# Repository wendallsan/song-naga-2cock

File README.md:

# Two-Headed Cockatrice  
### Double Deluxe Voltage Controlled Envelope Generator for Eurorack
  
Panel Concept Design  

## Features  
- Dual ADSR Envelopes with Gate and Trigger inputs and Voltage Control over each stage.  CV inputs for these controls are shared between both Envelopes with attenuverters for each for independently adjusting the resonse to incoming CV signals.  
- Envelope 2 includes a Voltage Controlled Gate Delay, and is triggered with Envelope 1 when nothing is plugged into its Gate or Trigger inputs.  
- Individual signal outputs for each Envelope and a Mix section, which outputs a mixed signal of both envelopes.  
- LED indicators of the output signals.  
- Fire button to manully trigger the Envelopes

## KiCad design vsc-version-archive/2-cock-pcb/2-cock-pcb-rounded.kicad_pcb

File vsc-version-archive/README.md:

# Two-Headed Cockatrice  
### Double Deluxe Voltage Controlled Envelope Generator for Eurorack

Panel Concept Design  

## Features  
- Dual ADSR Envelopes with Gate and Trigger inputs and Voltage Control over each stage.  CV inputs for these controls are shared between both Envelopes with attenuverters for each for independently adjusting the resonse to incoming CV signals.  
- Envelope 2 includes a Voltage Controlled Gate Delay, and is triggered with Envelope 1 when nothing is plugged into its Gate or Trigger inputs.  
- Individual signal outputs for each Envelope and a Mix section, which outputs a mixed signal of both envelopes.  
- LED indicators of the output signals.  
- Fire button to manully trigger the Envelopes

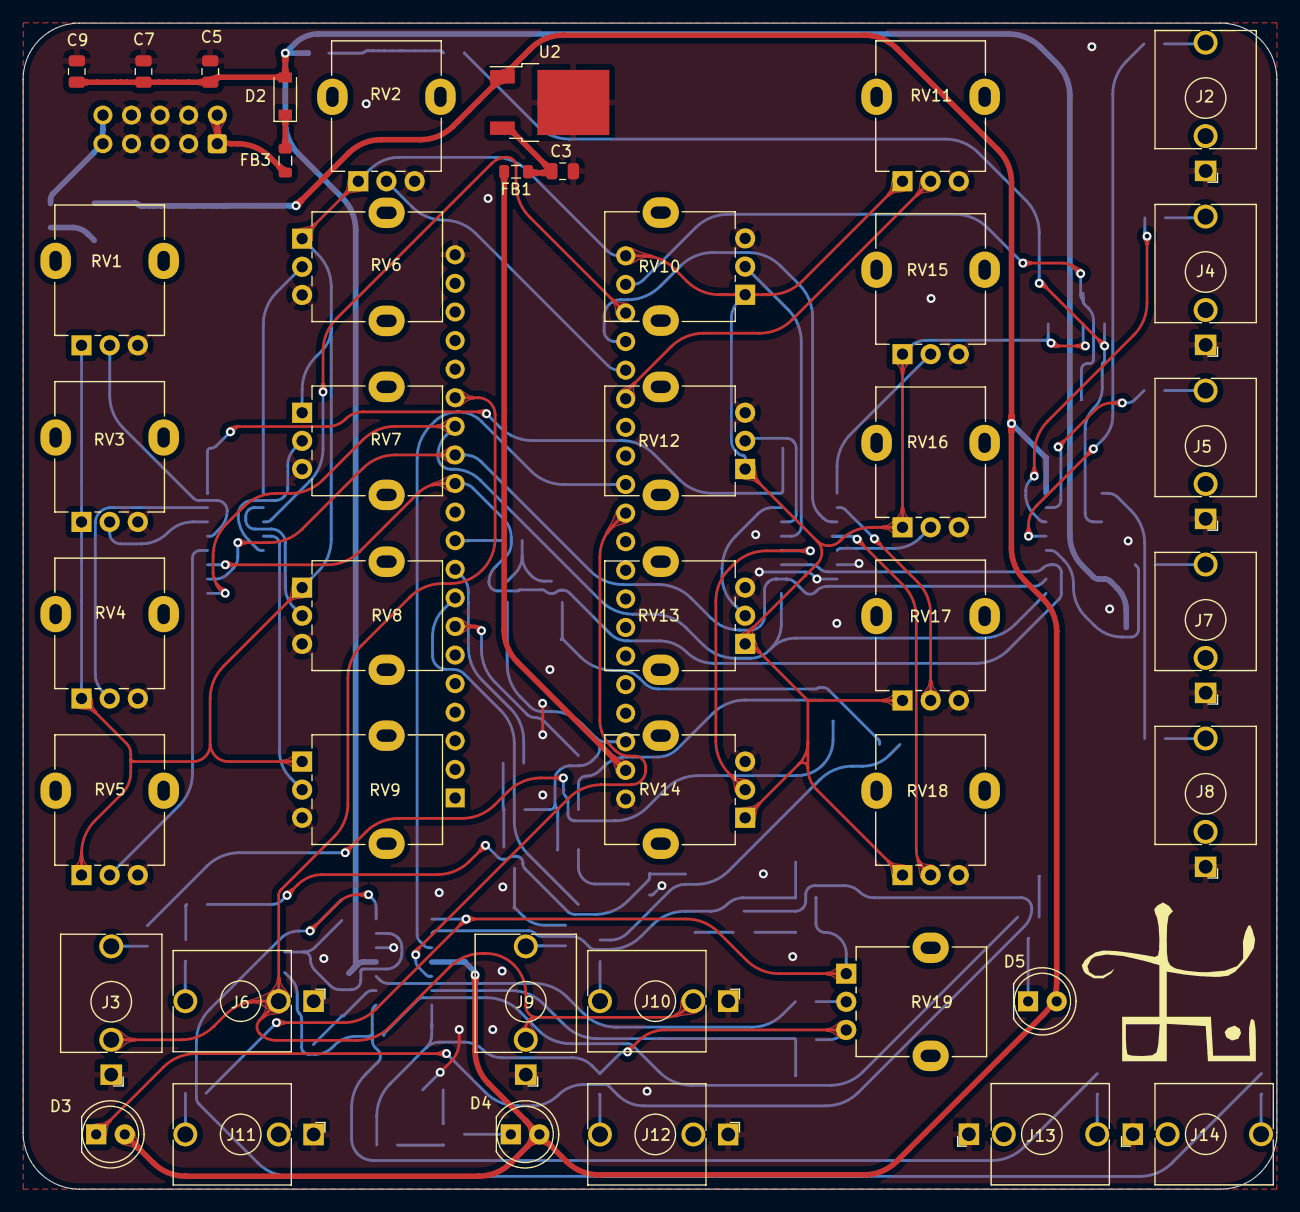
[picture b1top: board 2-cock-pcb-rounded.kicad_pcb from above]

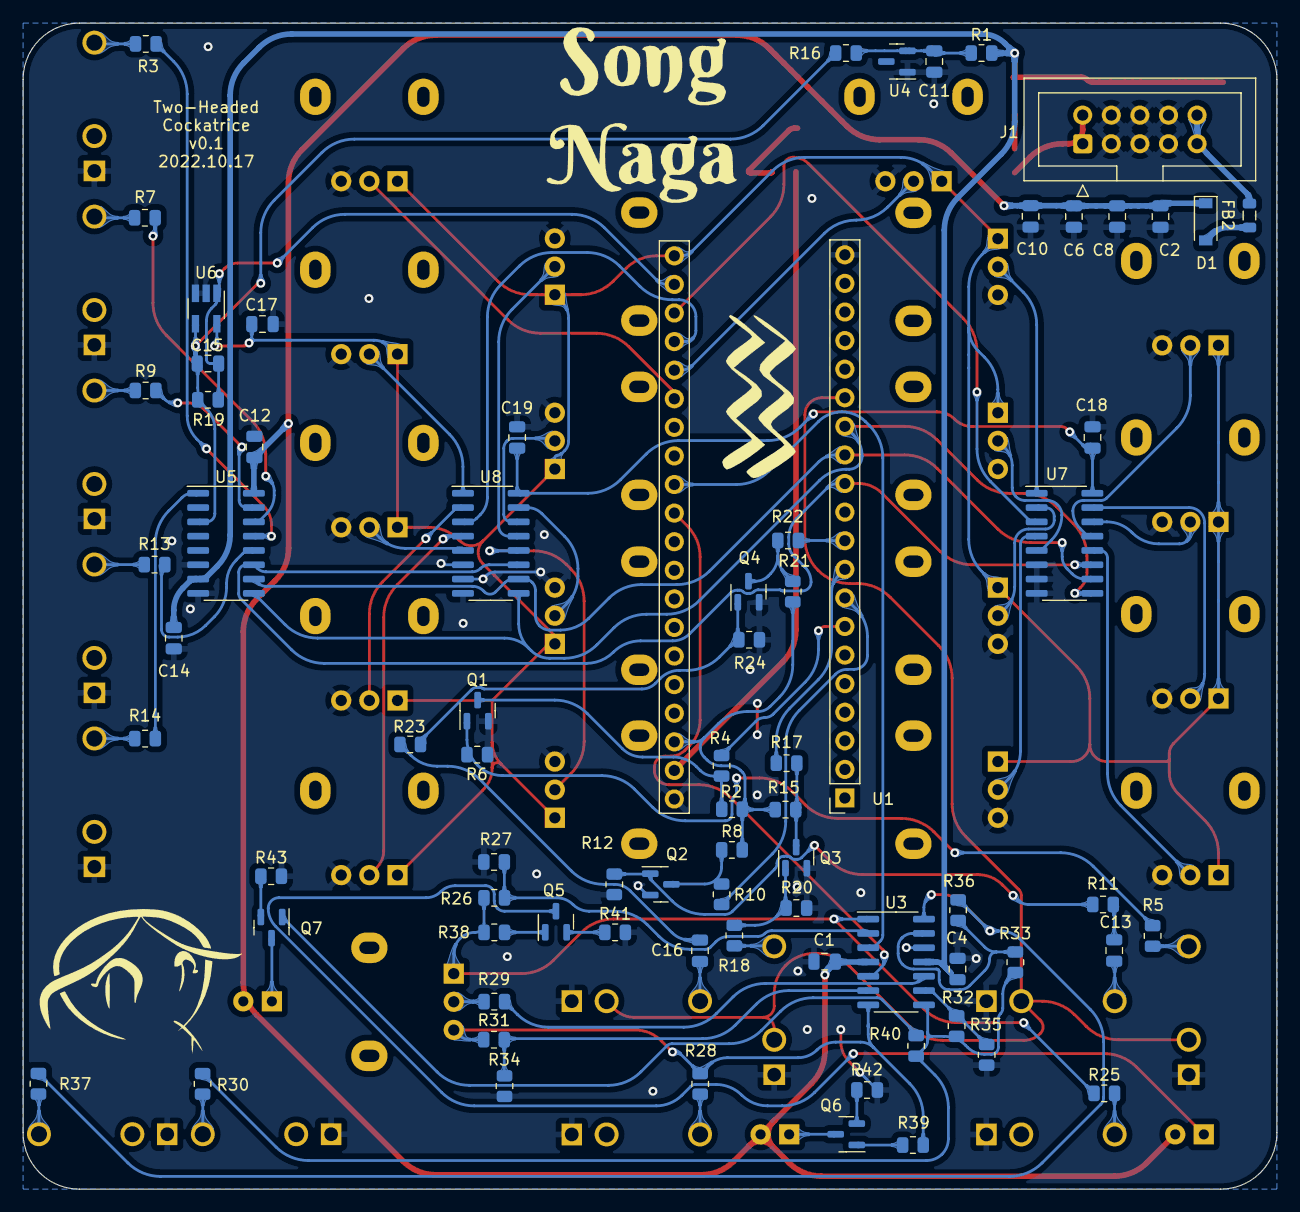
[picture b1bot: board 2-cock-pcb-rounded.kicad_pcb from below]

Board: 2 copper layers, 111.4 x 103.6 mm, 122 parts (78 on the bottom side), 92 nets.

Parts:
C1, C4, C12, C14, C15, C17, C18, C19: 10nF; C_0805_2012Metric
C2: 330nF; C_0805_2012Metric
C3, C7, C8, C9, C10, C11, C13, C16: 100nF; C_0805_2012Metric
C5, C6: 10uF; C_0805_2012Metric
D1, D2: D_Schottky; D_SOD-123
D3, D4, D5: LED; LED_D5.0mm
FB1, FB2, FB3: FerriteBead; L_0805_2012Metric
G1, G2, G3, G5: LOGO
J1: EURO_PWR_2x5; IDC-Header_2x05_P2.54mm_Vertical
J2: Delay CV In; Jack_3.5mm_QingPu_WQP-PJ398SM_Vertical_CircularHoles
J3: Gate 1; Jack_3.5mm_QingPu_WQP-PJ398SM_Vertical_CircularHoles
J4: Attack CV In; Jack_3.5mm_QingPu_WQP-PJ398SM_Vertical_CircularHoles
J5: Decay CV In; Jack_3.5mm_QingPu_WQP-PJ398SM_Vertical_CircularHoles
J6: Trigger 1; Jack_3.5mm_QingPu_WQP-PJ398SM_Vertical_CircularHoles
J7: Sustain CV In; Jack_3.5mm_QingPu_WQP-PJ398SM_Vertical_CircularHoles
J8: Release CV In; Jack_3.5mm_QingPu_WQP-PJ398SM_Vertical_CircularHoles
J9: Gate 2; Jack_3.5mm_QingPu_WQP-PJ398SM_Vertical_CircularHoles
J10: Trigger 2; Jack_3.5mm_QingPu_WQP-PJ398SM_Vertical_CircularHoles
J11: Out 1; Jack_3.5mm_QingPu_WQP-PJ398SM_Vertical_CircularHoles
J12: Out 2; Jack_3.5mm_QingPu_WQP-PJ398SM_Vertical_CircularHoles
J13: Mix Out; Jack_3.5mm_QingPu_WQP-PJ398SM_Vertical_CircularHoles
J14: Inv Out; Jack_3.5mm_QingPu_WQP-PJ398SM_Vertical_CircularHoles
Q1, Q2, Q3, Q4, Q5, Q6, Q7: MMBT3904; SOT-23
R1, R4, R10, R17, R22, R25, R28, R30, R37, R41, R42, R43: 1k; R_0805_2012Metric
R2, R15, R21, R38, R39, R40: 10k; R_0805_2012Metric
R3, R5, R7, R9, R11, R13, R14, R18, R23, R26, R29, R31, R32, R33, R35, R36: 100k; R_0805_2012Metric
R6, R12, R20, R24: 1M; R_0805_2012Metric
R8: R; R_0805_2012Metric
R16: 200k; R_0805_2012Metric
R19: 27k; R_0805_2012Metric
R27, R34: 50k; R_0805_2012Metric
RV1, RV2, RV3, RV4, RV5, RV6, RV7, RV8, RV9, RV10, RV11, RV12, RV13, RV14, RV15, RV16, RV17, RV18: 100k; Potentiometer_Alpha_RD901F-40-00D_Single_Vertical
RV19: B100k; Potentiometer_Alpha_RD901F-40-00D_Single_Vertical
U1: Daisy_Seed
U2: LM7805_TO220; TO-252-2
U3: TL074; SOIC-14_3.9x8.7mm_P1.27mm
U4: LM4040DBZ-10; SOT-23
U5, U7, U8: CD4051B; SOIC-16_3.9x9.9mm_P1.27mm
U6: MCP6001-OT; SOT-23-5_HandSoldering

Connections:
3V3_A: C17.1, RV1.1, RV2.1, RV3.1, RV4.1, RV5.1, RV6.1, RV7.1, RV8.1, RV9.1, RV10.1, RV11.1, RV12.1, RV13.1, RV14.1, RV15.1, RV16.1, RV17.1, RV18.1, U1.21 (+3V3_A), U6.5 (V+)
3V3_D: R2.2, R8.2, R15.2, R21.2, U1.38 (+3V3_D)
+3V3_A: C18.1, C19.1, U7.16 (VDD), U8.16 (VDD)
+5V: FB1.2, U1.39 (V_IN)
+12V: C1.1, C2.2, C6.1, C8.2, C10.2, C12.1, D1.1 (K), D3.2 (A), D4.2 (A), D5.2 (A), U2.1 (VI), U3.4 (V+), U5.16 (VDD)
-10V_REF: C11.2, R1.1, R16.1, U4.2 (A)
-12V: C4.1, C5.2, C7.1, C9.1, C14.1, D2.2 (A), R1.2, U3.11 (V-), U5.7 (VEE)
ADSR1_OUT: U1.29 (GPIO23(DAC1_OUT1)), U3.3 (+)
ADSR2_OUT: U1.30 (GPIO24(DAC1_OUT2)), U3.5 (+)
Attack 1: RV1.2, U7.13 (X0)
Attack 1 CV Adjust: RV10.2, U8.13 (X0)
Attack 2: RV6.2, U7.1 (X4)
Attack 2 CV Adjust: RV15.2, U8.1 (X4)
Attack CV: R7.2, U5.14 (X1)
CHANNEL SELECT A: U1.12 (GPIO12(I2C1_SCL)), U5.11 (A), U7.11 (A), U8.11 (A)
CHANNEL SELECT B: U1.13 (GPIO13(I2C1_SDA)), U5.10 (B), U7.10 (B), U8.10 (B)
CHANNEL SELECT C: U1.14 (GPIO14(USART1_TX)), U5.9 (C), U7.9 (C), U8.9 (C)
Decay 1: RV3.2, U7.14 (X1)
Decay 1 CV Adjust: RV12.2, U8.14 (X1)
Decay 2: RV7.2, U7.5 (X5)
Decay 2 CV Adjust: RV16.2, U8.5 (X5)
Decay CV: R9.2, U5.15 (X2)
Delay 2: RV2.2, U1.25 (GPIO19(ADC1_INP7))
Delay 2 CV Adjust: RV11.2, U1.26 (GPIO20(ADC1_INP3))
Delay CV: R3.2, U5.13 (X0)
GATE 1: R4.1, U1.7 (GPIO7(SDMMC1_CK))
GATE 2: R17.1, U1.9 (GPIO9(SPI1_SCK))
GND: C1.2, C2.1, C3.1, C4.2, C5.1, C6.2, C7.2, C8.1, C9.2, C10.1, C11.1, C12.2, C14.2, C17.2, C18.2, C19.2, J1.3 (GND), J1.4 (GND), J1.5 (GND), J1.6 (GND), J1.7 (GND), J1.8 (GND), J2.S, J3.S, J4.S, J5.S, J6.S, J7.S, J8.S, J9.S, J10.S, J11.S, J12.S, J13.S, J14.S, Q1.2 (E), Q2.2 (E), Q3.2 (E), Q4.2 (E), R6.1, R12.1, R20.1, R24.1, R27.1, R34.1, R35.1, R41.2, R42.2, R43.2, RV1.3, RV2.3, RV3.3, RV4.3, RV5.3, RV6.3, RV7.3, RV8.3, RV9.3, RV10.3, RV11.3, RV12.3, RV13.3, RV14.3, RV15.3, RV16.3, RV17.3, RV18.3, U1.20 (AGND), U1.40 (GND), U2.2 (GND), U3.12 (+), U4.1 (K), U5.6 (INH), U5.8 (VSS), U6.2 (V-), U6.3 (+), U7.6 (INH), U7.7 (VEE), U7.8 (VSS), U8.6 (INH), U8.7 (VEE), U8.8 (VSS)
MIX_LED: R30.1, R32.2, R33.1, R40.2, U3.8
MUXED SIGNAL 1: C15.2, R19.2, U1.22 (GPIO16(ADC1_INP10)), U6.1
MUXED SIGNAL 2: U1.23 (GPIO17(ADC1_INP15)), U7.3 (X)
MUXED SIGNAL 3: U1.24 (GPIO18(ADC1_INP5)), U8.3 (X)
NORMAL_PROBE: J3.TN, J6.TN, J9.TN, J10.TN, U1.15 (GPIO15(USART1_RX))
unnamed: C3.2, FB1.1, U2.3 (VO)
unnamed: C13.1, J6.T
unnamed: C13.2, R11.1
unnamed: C16.1, J10.T
unnamed: C16.2, R23.1
unnamed: D1.2 (A), FB2.2
unnamed: D2.1 (K), FB3.2
unnamed: D3.1 (K), Q5.3 (C)
unnamed: D4.1 (K), Q6.3 (C)
unnamed: D5.1 (K), Q7.3 (C)
unnamed: FB2.1, J1.9 (+12V), J1.10 (+12V)
unnamed: FB3.1, J1.1 (-12V), J1.2 (-12V)
unnamed: J2.T, R3.1
unnamed: J3.T, R5.1
unnamed: J4.T, R7.1
unnamed: J5.T, R9.1
unnamed: J7.T, R13.1
unnamed: J8.T, R14.1
unnamed: J9.T, R18.1
unnamed: J11.T, R25.2
unnamed: J12.T, R28.2
unnamed: J13.T, R30.2
unnamed: J14.T, R37.2
unnamed: Q1.1 (B), R5.2, R6.2
unnamed: Q1.3 (C), R2.1, R4.2
unnamed: Q2.1 (B), R11.2, R12.2
unnamed: Q2.3 (C), R8.1, R10.2
unnamed: Q3.1 (B), R18.2, R20.2
unnamed: Q3.3 (C), R15.1, R17.2
unnamed: Q4.1 (B), R23.2, R24.2
unnamed: Q4.3 (C), R21.1, R22.2
unnamed: Q5.1 (B), R38.1
unnamed: Q5.2 (E), R41.1
unnamed: Q6.1 (B), R39.1
unnamed: Q6.2 (E), R42.1
unnamed: Q7.1 (B), R40.1
unnamed: Q7.2 (E), R43.1
unnamed: R26.1, R27.2, U3.2 (-)
unnamed: R29.1, RV19.2
unnamed: R29.2, U3.10 (+)
unnamed: R31.1, R34.2, U3.6 (-)
unnamed: R32.1, R35.2, U3.9 (-)
unnamed: R33.2, R36.1, U3.13 (-)
unnamed: R36.2, R37.1, U3.14
OUT1_LED: R25.1, R26.2, R38.2, RV19.1, U3.1
OUT2_LED: R28.1, R31.2, R39.2, RV19.3, U3.7
Release 1: RV5.2, U7.12 (X3)
Release 1 CV Adjust: RV14.2, U8.12 (X3)
Release 2: RV9.2, U7.4 (X7)
Release 2 CV Adjust: RV18.2, U8.4 (X7)
Release CV: R14.2, U5.1 (X4)
Sustain 1: RV4.2, U7.15 (X2)
Sustain 1 CV Adjust: RV13.2, U8.15 (X2)
Sustain 2: RV8.2, U7.2 (X6)
Sustain 2 CV Adjust: RV17.2, U8.2 (X6)
Sustain CV: R13.2, U5.12 (X3)
TRIGGER 1: R10.1, U1.8 (GPIO8(SPI_NSS))
TRIGGER 2: R22.1, U1.10 (GPIO10(SPI1_MISO))
±10V MUXED SIGNAL: C15.1, R16.2, R19.1, U5.3 (X), U6.4 (-)

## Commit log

2022-08-17 initial commit. Basic working ADSR example with a button trigger.
2022-08-28 2cock.cpp: added mux handling, currently set up to handle adsr1 and adsr2 pots. Added adsr2. Added delaySignal ADC Channel for single input (doesn't fit on the mux). Updated DAC to output 2 channels 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
2022-09-01 DelayLine version of the delay control is place, not the effect I want, though!
2022-09-02 changed delayline to store the gate signal rather than the ADSR output. This works, except that the gate gets confused when pressing the trigger button more frequently than the gate time. I think we 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
2022-09-02 delayline is working! Added check for button release. Set delayTime as a class property so it can be set anywhere. Cleaned up setting delayTime from knob code. General code cleanup.
2022-09-11 Added gate and trigger sockets., which include normal detection on the sockets. Added initTriggersAndGates to set up IO pins and handleTriggersAndGates to handle interactions with those pins. Added n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
2022-10-13 added normalization probe features.
2022-11-26 Incremental commit: updates to 2cock.cpp to make it compatible with v0.1 board and initial testing notes and code. Added KiCAD files for reference.
2023-08-11 moved prior version's code to vsc-version-archive. added dev-files folder, which contains development files for adruino 2.0 IDE. Most current version as of this commit is muxed-dadsr.
